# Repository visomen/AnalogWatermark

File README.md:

Analog waveform generator, done as part of the NTNU's Self Defined Project course during my masters.

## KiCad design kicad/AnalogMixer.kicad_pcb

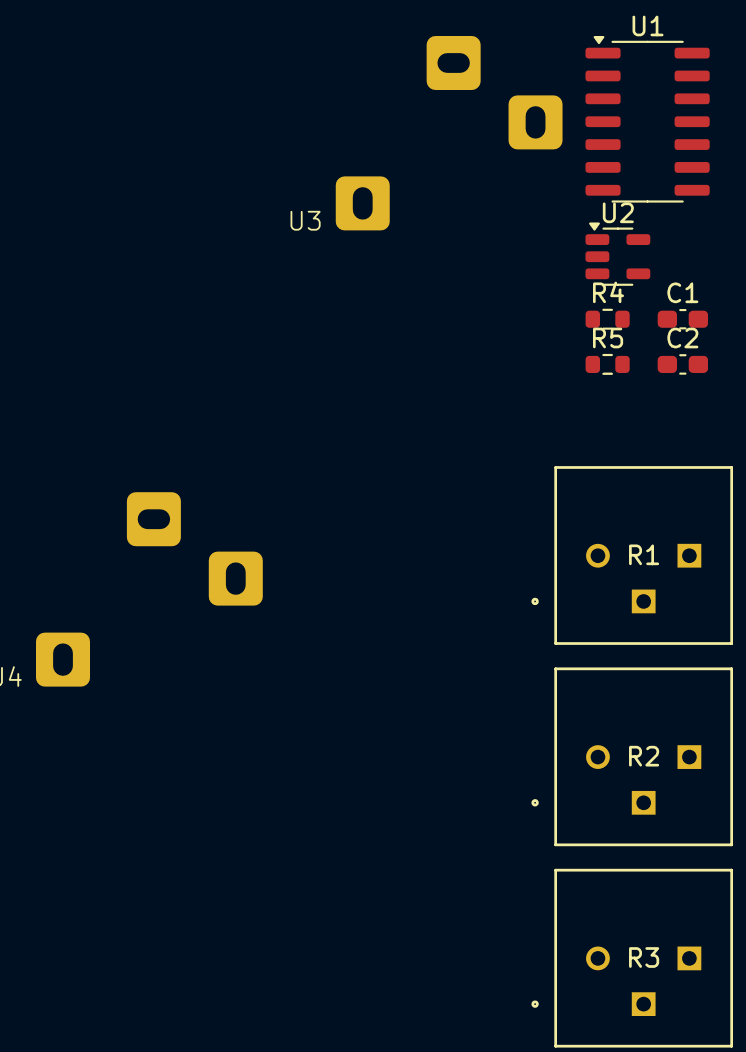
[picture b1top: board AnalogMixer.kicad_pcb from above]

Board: 2 copper layers, 11 parts (0 on the bottom side), 11 nets, no tracks yet.

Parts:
C1, C2: 1uF; C_0603_1608Metric_Pad1.08x0.95mm_HandSolder
R1, R2, R3: 3386P-1-103LF; POT_3386P
R4, R5: 10k; R_0603_1608Metric
U1: LM324; SOIC-14_3.9x8.7mm_P1.27mm
U2: MIC5317-3.3xM5; SOT-23-5
U3, U4: 3.5mm Socket

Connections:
+3.3V: C2.1, U1.4 (V+), U2.5 (VOUT)
/VOUT: R4.2, U1.8
GND: C1.2, C2.2, R1.3, R2.1, R3.1, U1.6 (-), U1.10 (+), U1.11 (V-), U2.2 (GND), U3.1 (SLEEVE), U4.1 (SLEEVE)
unnamed: R1.2, R5.1, U1.7
unnamed: U1.3 (+), U4.3 (TIP)
unnamed: R3.3, U1.1, U1.2 (-)
unnamed: R1.1, R2.2, R3.2, U1.5 (+)
unnamed: R4.1, R5.2, U1.9 (-)
unnamed: U1.12 (+), U3.3 (TIP)
unnamed: R2.3, U1.13 (-), U1.14
VDD: C1.1, U2.1 (VIN), U2.3 (EN)

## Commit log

2025-04-26 alfa version
